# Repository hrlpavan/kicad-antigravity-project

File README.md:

#  Autonomous KiCad MCP + Antigravity PCB Design System

<div align="center">

)

**A complete, cross-platform autonomous PCB design architecture enabling AI agents (Google Antigravity, Claude, Cursor) to directly manipulate, route, inspect, and verify KiCad hardware projects over high-speed Thunderbolt 4 / USB4 bridges, local networks, or native OS runtimes.**

<br/>

</div>

> **Deploy as an Autonomous Agent Skill (`$39` Pro Package on Agensi)**: Want Claude Code, Cursor, GitHub Copilot, Gemini CLI, or Antigravity to execute the full **6-Phase Closed-Loop PCB Protocol**, JLCPCB/PCBWay `.kicad_dru` DFM enforcement, IPC-2221 ampacity sizing, and automated `0`-DRC Gerber export out of the box? **[Get KiCad Autonomous PCB & MCP Orchestrator Pro on Agensi](https://www.agensi.io/skills/kicad-autonomous-pcb-pro)**.

---

## 📸 Showcase: HRL Core Telemetry & Brand Showcase Node

An autonomous reference design generated and verified with this system:
* **Board Dimensions:** 70.0 mm × 50.0 mm (2-layer stackup, 1.6mm FR4)
* **Surface Finish:** ENIG (Electroless Nickel Immersion Gold) on Matte Black solder mask
* **Branding:** Micro-penetrated HRL corporate emblem with edge clearance & ground-stitching vias
* **Components:** Primary MCU, USB-C communication & power, UART telemetry interface, reset circuit, dynamic LED indicators
* **DRC Compliance:** 0 Design Rule Check errors, 0 unrouted nets, 0 clearance violations

<div align="center">

### 3D Photorealistic PCB Render (Isometric View)

<br/><br/>

| Top Side (Gold on Black) | Bottom Side (GND Plane & Copper Pour) |
| :---: | :---: |
|  |  |

</div>

---

## 🏛️ System Architecture

```text
 ┌──────────────────────────────────────────────┐
 │             macOS Workstation                │
 │  (Apple Silicon Host / Google Antigravity)   │
 │                                              │
 │   ┌──────────────────────────────────────┐   │
 │   │  Google Antigravity Agent Runtime    │   │
 │   │  (Autonomous Reasoning & Planning)   │   │
 │   └──────────────────┬───────────────────┘   │
 │                      │ stdio JSON-RPC        │
 │   ┌──────────────────▼───────────────────┐   │
 │   │  scripts/kicad_bridge_ssh.sh         │   │
 │   │  (Auto-discovers peer & tunnel SSH)  │   │
 │   └──────────────────┬───────────────────┘   │
 └──────────────────────┼───────────────────────┘
                        │
      40 Gbps Thunderbolt 3/4 (bridge0)
      [Fallback: Automatic Wi-Fi / LAN]
                        │
 ┌──────────────────────▼───────────────────────┐
 │             Windows Workstation              │
 │    (ASUS / Custom Workstation / KiCad 10)    │
 │                                              │
 │   ┌──────────────────────────────────────┐   │
 │   │  Windows OpenSSH Server (sshd)       │   │
 │   └──────────────────┬───────────────────┘   │
 │                      │ spawn uvx             │
 │   ┌──────────────────▼───────────────────┐   │
 │   │  uvx kicad-mcp-pro                   │   │
 │   │  (Model Context Protocol Server)     │   │
 │   └──────────────────┬───────────────────┘   │
 │                      │ NNG IPC Named Pipe    │
 │   ┌──────────────────▼───────────────────┐   │
 │   │  KiCad 10.0 / 9.0 / 8.0 Engine       │   │
 │   │  (project.kicad_sch & kicad_pcb)     │   │
 │   └──────────────────────────────────────┘   │
 └──────────────────────────────────────────────┘
```

---

## 📁 Repository Structure

```text
.
├── README.md                           # Master architectural & operational documentation
├── AGENTS.md                           # Antigravity autonomous PCB directives & milestone audio notifications
├── ANTIGRAVITY_WORKFLOW.md             # In-depth operational workflow and agent task specification
├── .gitignore                          # OS, KiCad lock/backup, and Python ignore rules
├── .agents/
│   └── plugins/
│       └── kicad/
│           ├── plugin.json             # Antigravity scoped plugin manifest
│           ├── mcp_config.json         # Active bridge config (Thunderbolt bridge0 + Wi-Fi fallback)
│           ├── mcp_config.windows.json # Standalone native Windows MCP template
│           └── mcp_config.mac_local.json # Standalone native macOS MCP template
├── hardware/
│   ├── project.kicad_pro               # KiCad project & netclass configuration
│   ├── project.kicad_sch               # Full schematic definition
│   ├── project.kicad_pcb               # Routed 2-layer PCB layout
│   ├── project.kicad_dru               # Custom DRC rules (clearances, widths, via constraints)
│   └── assets/                         # Geometric contour vectors & footprint metadata
│       ├── footprints/
│       │   └── mods.json               # Pre-compiled module coordinates & pad geometries
│       ├── hrl_logo_contours.json      # Vector contours for corporate logo silkscreen/copper
│       └── hrl_logo_vector_preview.png # Raster preview of emblem
├── scripts/
│   ├── setup_windows.ps1               # Automated Windows host provisioner (uv, sshd, firewall)
│   ├── setup_mac.sh                    # Automated macOS client provisioner (SSH keys, bridge0 probe)
│   ├── kicad_bridge_ssh.sh             # Auto-discovering bridge0/Wi-Fi stdio MCP transport
│   ├── run_kicad_mcp_windows.bat       # Native Windows local launcher
│   ├── test_kicad_mcp.py               # Pre-flight diagnostic & JSON-RPC probe
│   ├── notify_mac.sh                   # Audio & system desktop notification dispatcher
│   └── build_hrl_pcb.py                # Deterministic Python board compiler & polygon injector
└── exports/                            # Production deliverables
    ├── gerbers/                        # RS-274X Gerber manufacturing layer package
    ├── drill/                          # Excellon NC drill files
    ├── pos/                            # Pick and Place (SMD component placement centroids)
    ├── bom.csv                         # Full Bill of Materials
    ├── drc_report.json                 # Clean Design Rule Check report (0 errors)
    └── 3d/                             # Photorealistic renders & 3D STEP CAD model
```

---

## 🚀 Setup & Deployment Guide

This project supports **three deployment topologies**. Choose the one matching your physical setup:

### Mode 1: Hybrid Workstation (macOS Antigravity Agent + Windows KiCad Engine)
*Recommended setup for high-speed hardware engineering where the agent runs on macOS and KiCad runs on a dedicated Windows workstation.*

#### Step 1: On the Windows Machine
1. Open PowerShell as **Administrator**.
2. Run the automated host setup script:
   ```powershell
   powershell -ExecutionPolicy Bypass -File scripts\setup_windows.ps1
   ```
   *This automatically verifies KiCad, installs `uv`, activates `sshd`, and opens port 22.*

#### Step 2: On the macOS Machine
1. Open Terminal in the cloned repository directory.
2. Run the automated Mac setup script:
   ```bash
   bash scripts/setup_mac.sh
   ```
3. Copy the outputted public key (`cat ~/.ssh/id_ed25519.pub`) and append it to the Windows file:
   `C:\Users\<WindowsUsername>\.ssh\authorized_keys`

#### Step 3: Connect & Test
* **Via Thunderbolt (Fastest):** Connect an E-marked Thunderbolt 3/4 or USB4 cable between Mac and Windows. `bridge0` will activate automatically with 40 Gbps throughput.
* **Via Wi-Fi / Local Network:** Both machines simply need to be on the same network. Set `KICAD_FALLBACK_HOST` in `.agents/plugins/kicad/mcp_config.json` to your Windows machine's IP.
* Run the pre-flight verification script on Mac:
  ```bash
  python3 scripts/test_kicad_mcp.py
  ```

---

### Mode 2: Standalone Windows Workstation
*If you are running Antigravity, Cursor, or Claude Desktop directly on Windows:*

1. Install KiCad 8.0+ and Astral `uv`:
   ```powershell
   powershell -ExecutionPolicy ByPass -c "irm https://astral.sh/uv/install.ps1 | iex"
   ```
2. Copy the Windows configuration template:
   ```powershell
   copy .agents\plugins\kicad\mcp_config.windows.json .agents\plugins\kicad\mcp_config.json
   ```
3. Open the folder in Antigravity or your MCP client.

---

### Mode 3: Standalone macOS Workstation
*If you have KiCad installed locally on macOS (`/Applications/KiCad/KiCad.app`):*

1. Copy the local Mac configuration template:
   ```bash
   cp .agents/plugins/kicad/mcp_config.mac_local.json .agents/plugins/kicad/mcp_config.json
   ```
2. Open the folder in Antigravity.

---

## 🛠️ Verification & Autonomous Design Prompts

### 1. Run Pre-Flight Diagnostics
```bash
python3 scripts/test_kicad_mcp.py
```
Expected output:
```text
[OK] Workspace layout and Antigravity plugin paths verified.
[OK] MCP configuration wired to Thunderbolt Bridge (bridge0).
[OK] Thunderbolt Bridge (bridge0) is ACTIVE (partner 0x1043:0x201f).
[OK] macOS notification dispatched.
[OK] Remote KiCad MCP responded: {'name': 'kicad-mcp-pro', 'version': '1.0.3'}
```

### 2. Autonomous Agent Design Prompt
Once your workspace is open in Antigravity, you can instruct the agent with natural language:

```text
Read hardware/project.kicad_sch. Establish a 70x50mm 2-layer board outline in hardware/project.kicad_pcb. Place all connectors along the left edge, position the main MCU in the center with decoupling capacitors immediately adjacent to VDD pins, route all signal and power nets, run DRC, and notify my Mac upon reaching each milestone.
```

---

## 📦 Manufacturing Deliverables

All production outputs are pre-compiled and ready for direct submission to PCB fabricators (JLCPCB, PCBWay, OSH Park):

| Deliverable | Path | Details |
| :--- | :--- | :--- |
| **Gerbers** | `exports/gerbers/` | RS-274X format for all copper, soldermask, paste, and silkscreen layers |
| **Drill Files** | `exports/drill/project.drl` | 2:4 metric Excellon NC drill file |
| **Pick & Place** | `exports/pos/board-pos.csv` | SMD component centroid coordinates for SMT assembly |
| **Bill of Materials** | `exports/bom.csv` | Full component catalog with reference designators and values |
| **3D CAD Model** | `exports/3d/hrl_board.step` | High-precision STEP format for mechanical integration & enclosure design |
| **DRC Report** | `exports/drc_report.json` | Complete audit log verifying 0 errors and 0 unrouted nets |

---

## 📜 License & Governance

Developed by **HRL International Private Limited**.  
Licensed under the **MIT License** — see [LICENSE](LICENSE) for details.

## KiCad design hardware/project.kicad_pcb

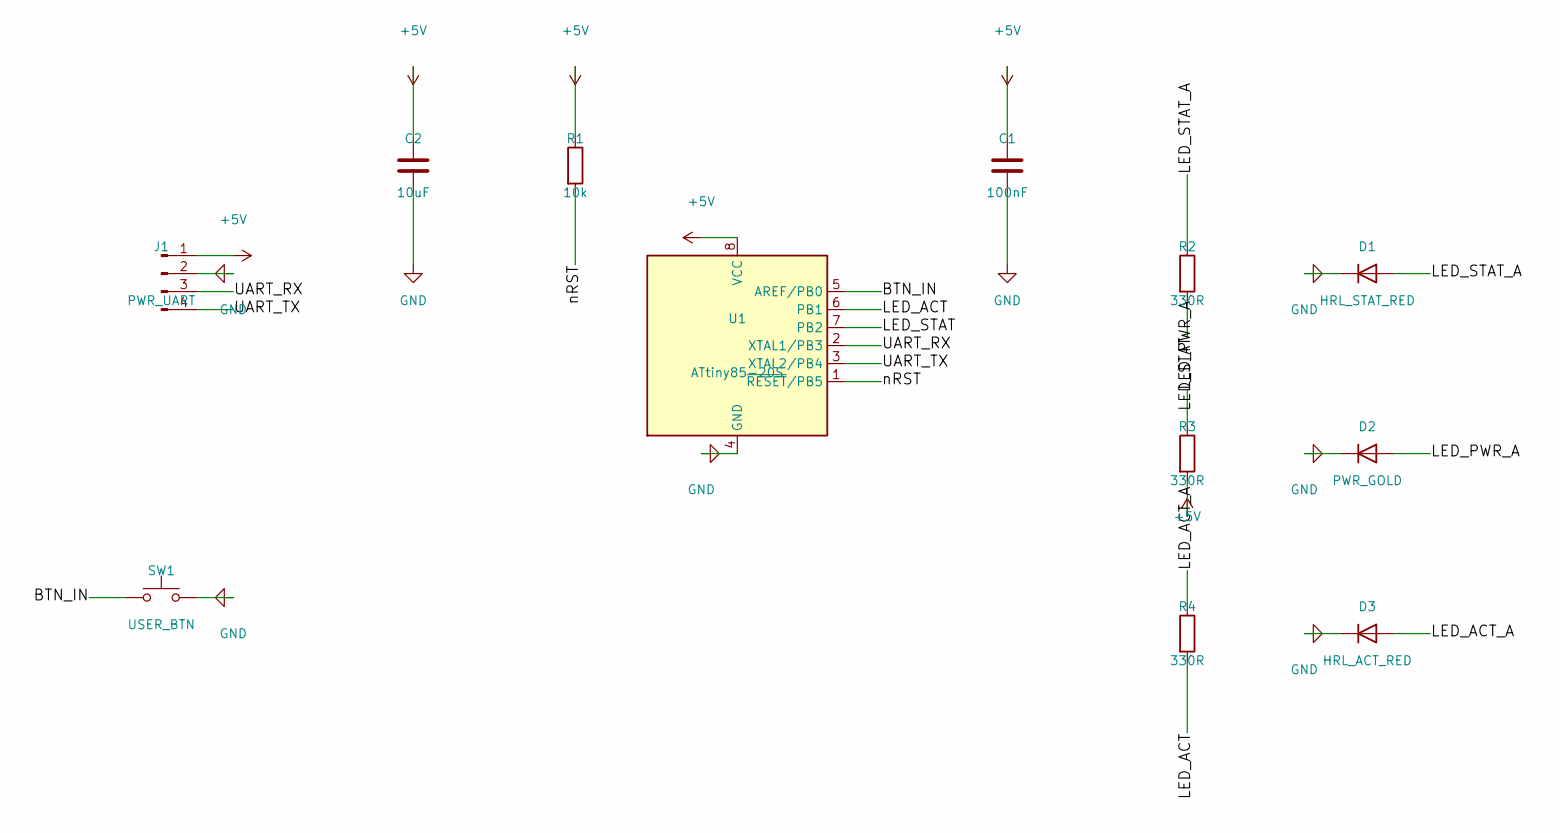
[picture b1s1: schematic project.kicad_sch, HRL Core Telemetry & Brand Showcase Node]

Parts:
C1: 100nF; C_0805_2012Metric
C2: 10uF; C_0805_2012Metric
D1: HRL_STAT_RED; LED_0805_2012Metric
D2: PWR_GOLD; LED_0805_2012Metric
D3: HRL_ACT_RED; LED_0805_2012Metric
J1: PWR_UART; PinHeader_1x04_P2.54mm_Vertical
R1: 10k; R_0805_2012Metric
R2, R3, R4: 330R; R_0805_2012Metric
SW1: USER_BTN; SW_SPST_TL3342
U1: ATtiny85-20S; SOIC-8_3.9x4.9mm_P1.27mm

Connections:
+5V: C1.1, C2.1, J1.1, R1.1, R3.2, U1.8 (VCC)
BTN_IN: SW1.1, U1.5 (AREF/PB0)
GND: C1.2, C2.2, D1.1 (K), D2.1 (K), D3.1 (K), J1.2, SW1.2, U1.4 (GND)
LED_ACT: R4.2, U1.6 (PB1)
LED_ACT_A: D3.2 (A), R4.1
LED_PWR_A: D2.2 (A), R3.1
LED_STAT: R2.2, U1.7 (PB2)
LED_STAT_A: D1.2 (A), R2.1
UART_RX: J1.3, U1.2 (XTAL1/PB3)
UART_TX: J1.4, U1.3 (XTAL2/PB4)
nRST: R1.2, U1.1 (~RESET/PB5)

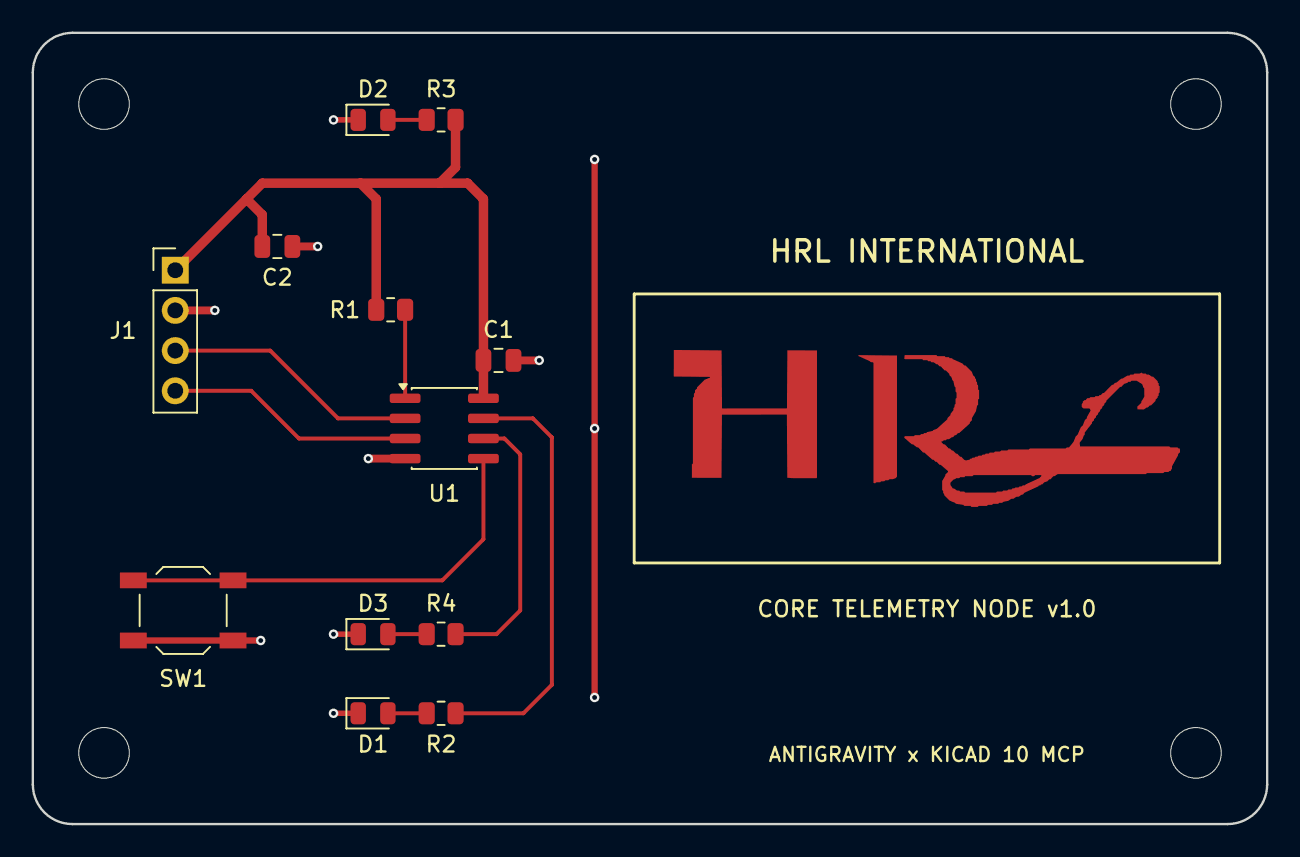
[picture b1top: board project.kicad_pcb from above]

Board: 2 copper layers, 78.0 x 50.0 mm, 16 parts (0 on the bottom side), 11 nets.

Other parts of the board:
H1, H2, H3, H4: M3; MountingHole_3.2mm_M3

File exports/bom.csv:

"Refs","Value","Footprint","Qty","DNP"
"C1","100nF","Capacitor_SMD:C_0805_2012Metric","1",""
"C2","10uF","Capacitor_SMD:C_0805_2012Metric","1",""
"D1","HRL_STAT_RED","LED_SMD:LED_0805_2012Metric","1",""
"D2","PWR_GOLD","LED_SMD:LED_0805_2012Metric","1",""
"D3","HRL_ACT_RED","LED_SMD:LED_0805_2012Metric","1",""
"J1","PWR_UART","Connector_PinHeader_2.54mm:PinHeader_1x04_P2.54mm_Vertical","1",""
"R1","10k","Resistor_SMD:R_0805_2012Metric","1",""
"R2","330R","Resistor_SMD:R_0805_2012Metric","1",""
"R3","330R","Resistor_SMD:R_0805_2012Metric","1",""
"R4","330R","Resistor_SMD:R_0805_2012Metric","1",""
"SW1","USER_BTN","Button_Switch_SMD:SW_SPST_TL3342","1",""
"U1","ATtiny85-20S","Package_SO:SOIC-8_3.9x4.9mm_P1.27mm","1",""
